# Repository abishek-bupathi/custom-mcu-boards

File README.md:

<h1 align="center">Custom Microcontroller Boards</h1>

## STM32F1-BMGP

### Features
- Bare Minimum General Purpose (BMGP) board based on STM32F103C8T Microcontroller
- 16 Mhz Clock
- Operating at 3.3 V
- Peripherals: 1xI2C, 1xSPI, 1xUART
- Connectivity: USB 2.0 Type C

### Schematics

### PCB Layout

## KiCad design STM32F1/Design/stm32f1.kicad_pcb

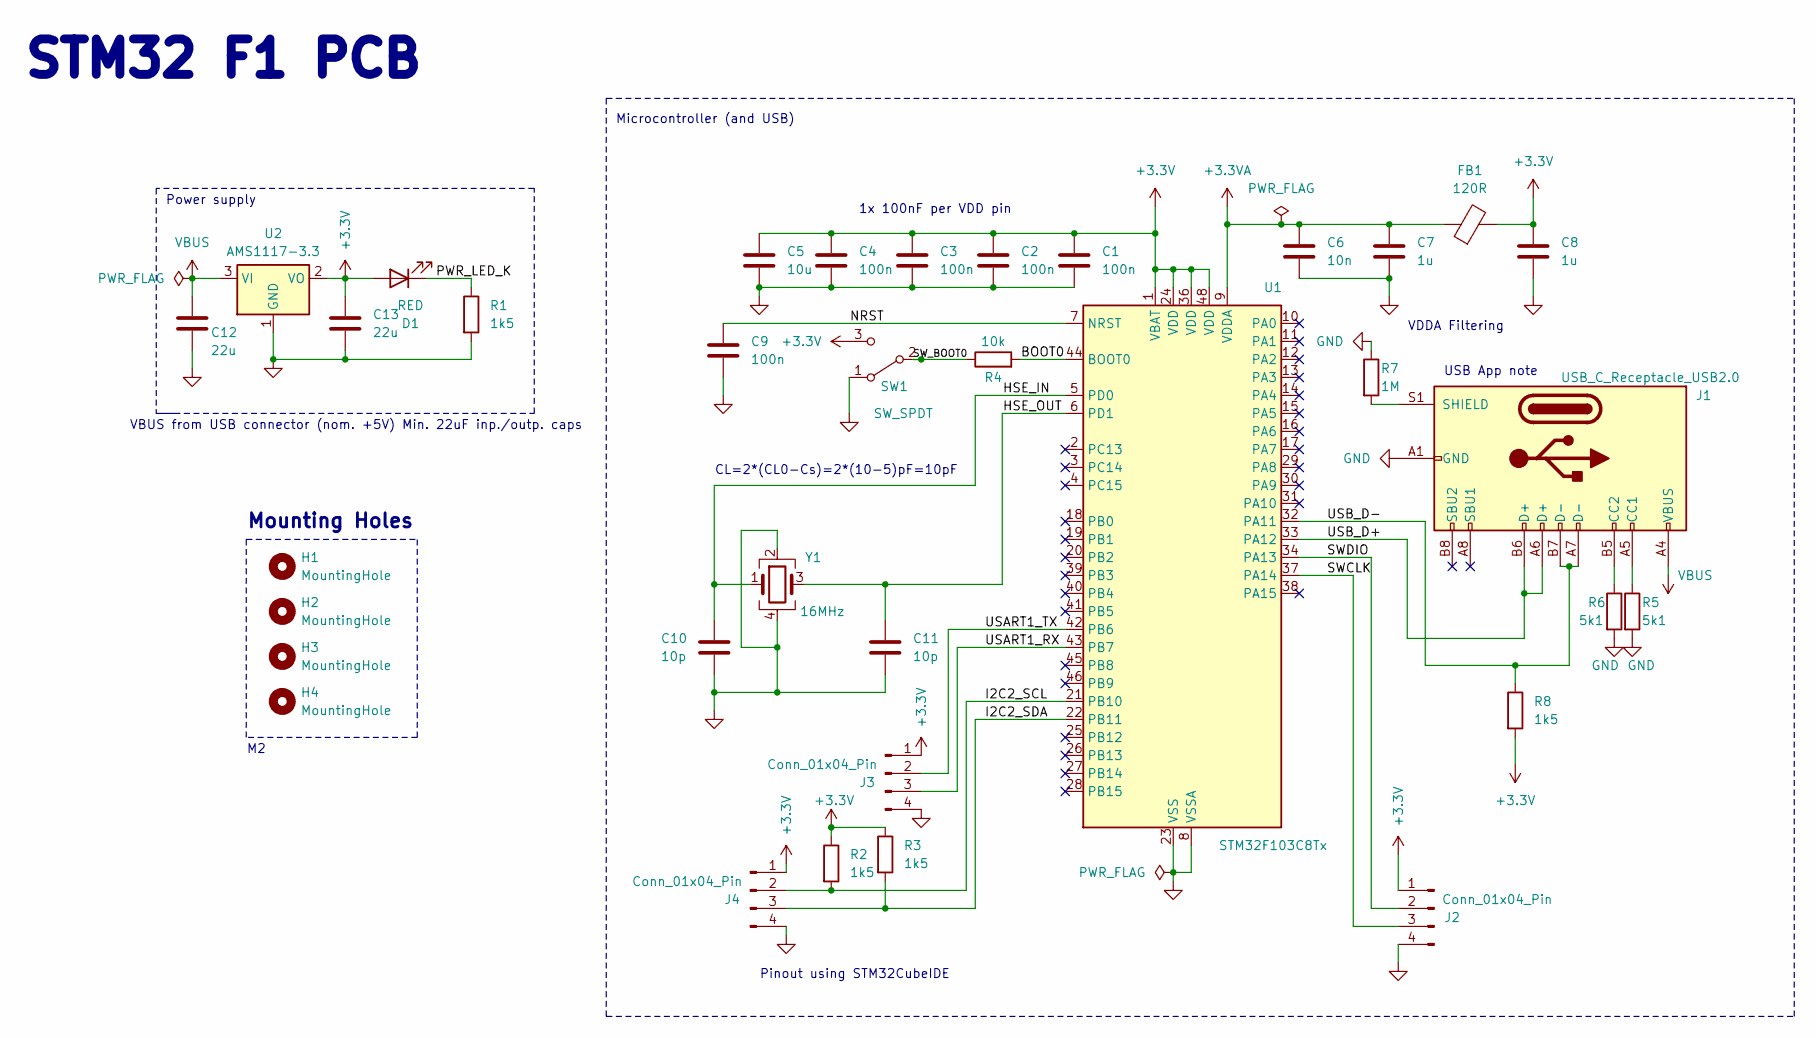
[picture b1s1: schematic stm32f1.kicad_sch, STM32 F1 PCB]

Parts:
C1, C2, C3, C4, C9: 100n; C_0402_1005Metric
C5: 10u; C_0603_1608Metric
C6: 10n; C_0402_1005Metric
C7, C8: 1u; C_0402_1005Metric
C10, C11: 10p; C_0402_1005Metric
C12, C13: 22u; C_0805_2012Metric
D1: RED; LED_0603_1608Metric
FB1: 120R; L_0603_1608Metric
H1, H2, H3, H4: MountingHole; MountingHole_2.2mm_M2
J1: USB_C_Receptacle_USB2.0; USB_C_Receptacle_HRO_TYPE-C-31-M-12
J2, J3, J4: Conn_01x04_Pin; PinHeader_1x04_P2.54mm_Vertical
R1, R2, R3, R8: 1k5; R_0402_1005Metric
R4: 10k; R_0402_1005Metric
R5, R6: 5k1; R_0402_1005Metric
R7: 1M; R_0402_1005Metric
SW1: SW_SPDT; SW_SPDT_PCM12
U1: STM32F103C8Tx; LQFP-48_7x7mm_P0.5mm
U2: AMS1117-3.3; SOT-223-3_TabPin2
Y1: 16MHz; Crystal_SMD_3225-4Pin_3.2x2.5mm

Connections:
+3.3V: C1.1, C2.1, C3.1, C4.1, C5.1, C8.1, C13.1, D1.2 (A), FB1.2, J2.1, J3.1, J4.1, R2.1, R3.1, R8.2, SW1.3 (C), U1.1 (VBAT), U1.24 (VDD), U1.36 (VDD), U1.48 (VDD), U2.2 (VO)
+3.3VA: C6.1, C7.1, FB1.1, U1.9 (VDDA)
/BOOT0: R4.2, U1.44 (BOOT0)
/HSE_IN: C10.1, U1.5 (PD0), Y1.1
/HSE_OUT: C11.1, U1.6 (PD1), Y1.3
/I2C2_SCL: J4.2, R2.2, U1.21 (PB10)
/I2C2_SDA: J4.3, R3.2, U1.22 (PB11)
/NRST: C9.1, U1.7 (NRST)
/PWR_LED_K: D1.1 (K), R1.1
/SWCLK: J2.3, U1.37 (PA14)
/SWDIO: J2.2, U1.34 (PA13)
/SW_BOOT0: R4.1, SW1.2 (B)
/USART1_RX: J3.3, U1.43 (PB7)
/USART1_TX: J3.2, U1.42 (PB6)
/USB_D+: J1.A6 (D+), J1.B6 (D+), U1.33 (PA12)
/USB_D-: J1.A7 (D-), J1.B7 (D-), R8.1, U1.32 (PA11)
GND: C1.2, C2.2, C3.2, C4.2, C5.2, C6.2, C7.2, C8.2, C9.2, C10.2, C11.2, C12.2, C13.2, J1.A1 (GND), J1.A12 (GND), J1.B1 (GND), J1.B12 (GND), J2.4, J3.4, J4.4, R1.2, R5.2, R6.2, R7.1, SW1.1 (A), U1.8 (VSSA), U1.23 (VSS), U1.35 (VSS), U1.47 (VSS), U2.1 (GND), Y1.2, Y1.4
unnamed: J1.A5 (CC1), R5.1
unnamed: J1.B5 (CC2), R6.1
unnamed: J1.S1 (SHIELD), R7.2
VBUS: C12.1, J1.A4 (VBUS), J1.A9 (VBUS), J1.B4 (VBUS), J1.B9 (VBUS), U2.3 (VI)

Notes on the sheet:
Power supply
VBUS from USB connector (nom. +5V) Min. 22uF inp./outp. caps
Microcontroller (and USB)
1x 100nF per VDD pin
USB App note
VDDA Filtering
CL=2*(CL0-Cs)=2*(10-5)pF=10pF
Pinout using STM32CubeIDE
STM32 F1 PCB
Mounting Holes

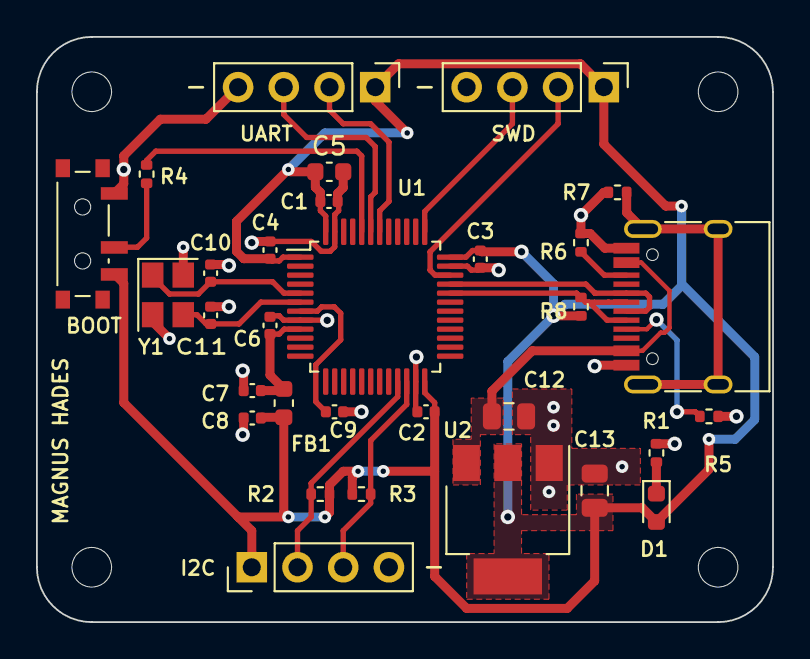
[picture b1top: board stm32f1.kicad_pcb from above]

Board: 2 copper layers, 40.9 x 32.5 mm, 35 parts (0 on the bottom side), 21 nets.

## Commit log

2023-10-05 Added power and pinout circuit
2023-12-08 Completed schematics and added PCB layout
2023-12-10 Fine tunes PCB layout and added borders, Started routing
2023-12-20 Completed Board design
2023-12-20 Removed unwanted files
2023-12-21 Added production files
2023-12-24 Design, BOM, CPL and Gerber files complete
2023-12-30 Added documents
2023-12-30 Renamed project
